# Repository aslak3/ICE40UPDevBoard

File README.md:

# ICE40UPDevBoard: an iCE40UP5K development board

## Features

The specification for this development board is as follows:

* [iCE40UP5K](https://www.latticesemi.com/view_document?document_id=51968) in QFN
* [N25Q032A](https://docs.rs-online.com/0866/0900766b80f7f8ab.pdf) 32 Mbit SPI flash
* DB15 VGA port:
  * [ADV7123](https://www.analog.com/media/en/technical-documentation/data-sheets/ADV7123-EP.pdf) RGB DAC
* PS/2 port with two channels for a mouse and keyboard
* I2C:
  * [DS3231M](https://www.analog.com/media/en/technical-documentation/data-sheets/ds3231m.pdf) RTC
  * [AT24C64](https://ww1.microchip.com/downloads/en/devicedoc/doc0336.pdf) EEPROM
  * Header for I2C connections
* 3 LEDs and a button
* User header with 6 available FPGA pins
* Powered by a 5V switching regulator (eg a 5V [PM05S050A](https://filecenter.deltaww.com/products/download/01/0102/datasheet/DS_PM05S.pdf)) and a barrel jack

A [schematic](ICE40UPDevBoard.pdf) is included here, along with the
[KiCAD](https://www.kicad.org) data files, whcih are in  KiCAD 6 format.

## PCB design

The PCB is a 4 layer board.  My boards were manufactured by
[JLCPCB](https://www.jlcpcb.com).

## Using

The jumper mechanism to route the SPI signals which carry the configuration
data from the programmer was borrowed directly from the [Lattice’s iCE40
UltraPlus Breakout
Board](https://www.latticesemi.com/view_document?document_id=51987).

Any iCE40 compatible programmer should be useable.  I built my own, out of a
Pi Pico, which is documented in [another repo](https://github.com/aslak3/spi-flasher).
The programmer has been used to program both the attached flash and the FPGA directly.

## Possible gotchas

The design of this board is a very slightly tweaked version of the build I
have on my bench.  I have tweaked the LED and button connection after
finding out that the three LED pins on the iCE40UP cannot source current for
an LED and must sink it instead.

The following features have not been tested yet:

* I2C bus and peripheral ICs
* PS/2 port

## Blog

The best place to learn about this board is undoubtably [my
blog](https://www.aslak.net/), including this post:

* [Design and build of a Lattice iCE40UP development board](https://www.aslak.net/index.php/2024/01/31/design-and-build-of-a-lattice-ice40up-development-board/)

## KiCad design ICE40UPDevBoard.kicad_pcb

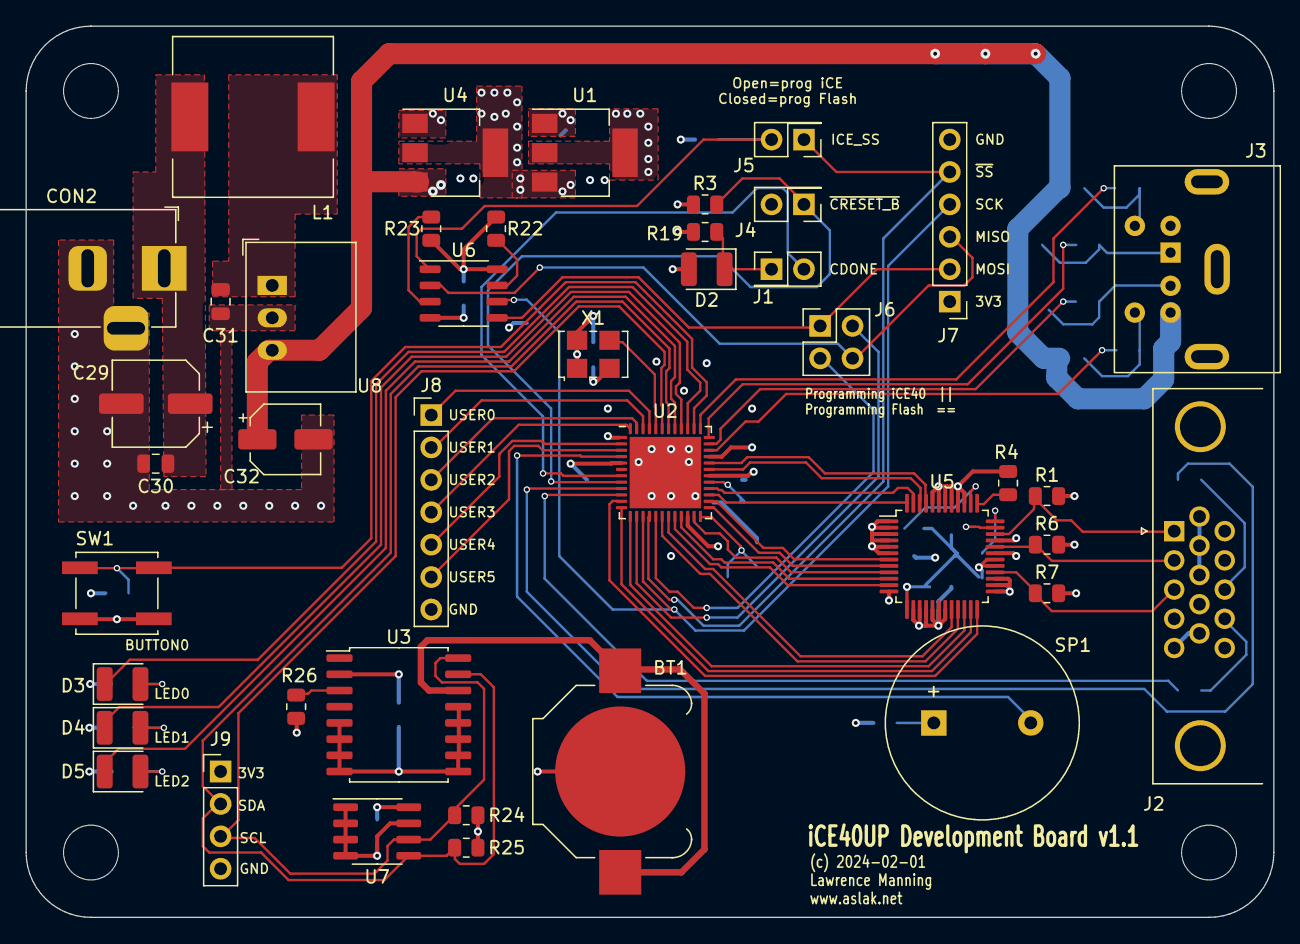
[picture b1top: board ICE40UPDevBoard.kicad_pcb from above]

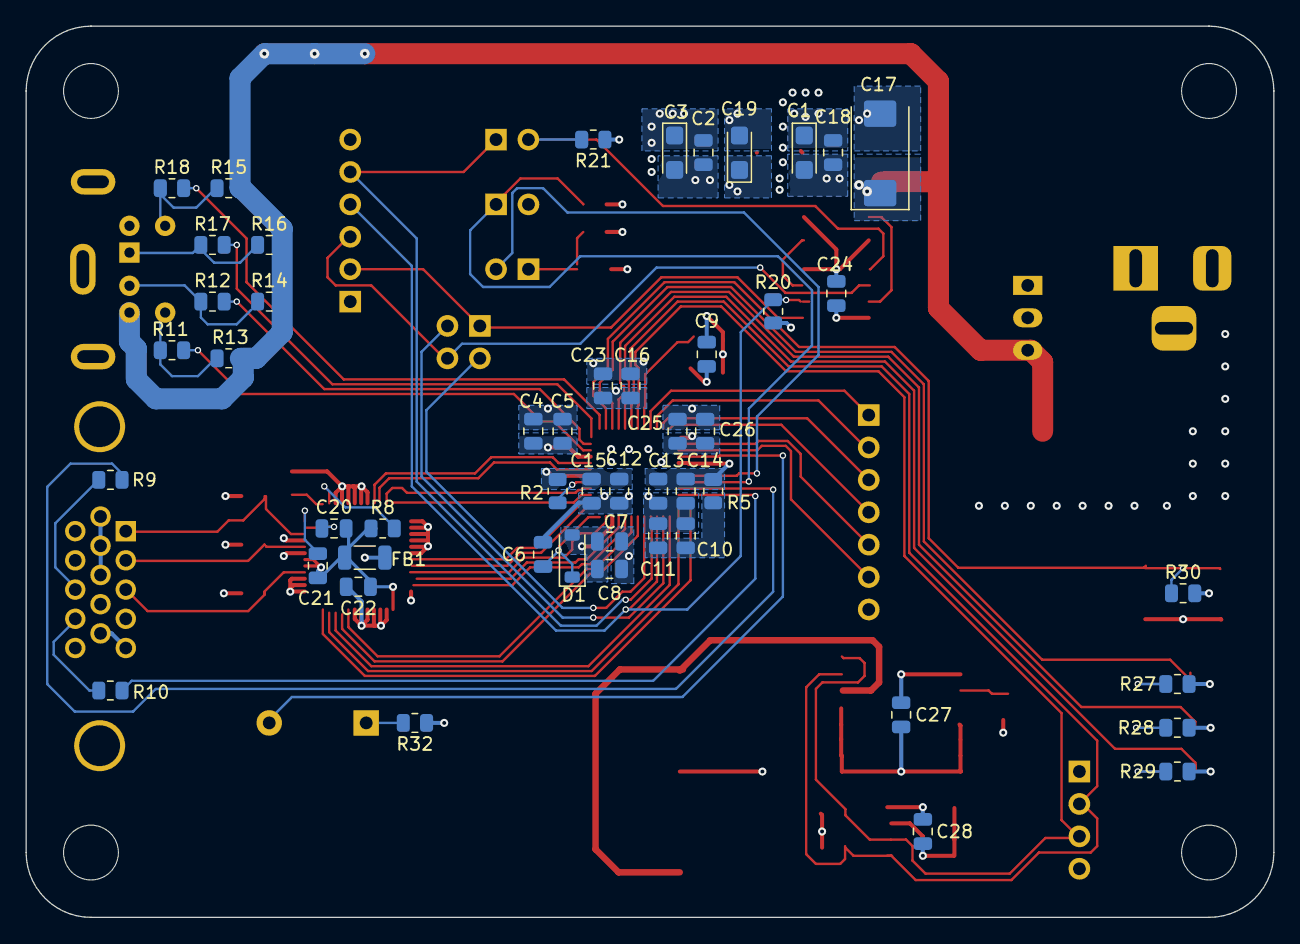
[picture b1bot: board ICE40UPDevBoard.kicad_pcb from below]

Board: 4 copper layers, 97.8 x 69.8 mm, 96 parts (50 on the bottom side), 75 nets.

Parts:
BT1: Battery_Cell; BatteryHolder_Keystone_3000_1x12mm
C1, C3, C19: 10u; CP_EIA-3216-10_Kemet-I
C2, C4, C6, C7, C9, C12, C13, C18, C20, C21, C22, C24, C25, C27, C28: 0.1u; C_0805_2012Metric
C5, C8, C14, C15, C26: 10n; C_0805_2012Metric
C10, C16, C30: 10u; C_0805_2012Metric
C11, C23: 100n; C_0805_2012Metric
C17: 47u; CP_EIA-7343-15_Kemet-W
C29: 470u; CP_Elec_6.3x7.7
C31: 4.7u; C_0805_2012Metric
C32: 10u; CP_Elec_5x5.7
CON2: POWERLJACK; BarrelJack_Horizontal
D1: MBR130; D_SOD-123
D2, D3, D4, D5: CDONE_LED; LED_1210_3225Metric
FB1: Bead; L_1206_3216Metric
H1, H2, H3, H4: HOLE; MountingHole_4.3mm_M4
J1, J4, J5: Conn_02x01; PinHeader_2x01_P2.54mm_Vertical
J2: DB15HD_FEMALE_SVGA; DSUB-15-HD_Female_Horizontal_P2.29x1.98mm_EdgePinOffset3.03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
J3: Mini-DIN-6; Connector_Mini-DIN_Female_6Pin_2rows
J6: Conn_02x02_Odd_Even; PinHeader_2x02_P2.54mm_Vertical
J7: Conn_01x06; PinHeader_1x06_P2.54mm_Vertical
J8: Conn_01x07; PinHeader_1x07_P2.54mm_Vertical
J9: Conn_01x04; PinHeader_1x04_P2.54mm_Vertical
L1: 10u; L_12x12mm_H4.5mm
R1, R6, R7: 75; R_0805_2012Metric
R2, R5: 100; R_0805_2012Metric
R3, R20, R21, R22, R23: 10K; R_0805_2012Metric
R4: 530; R_0805_2012Metric
R8, R13, R14, R15, R16, R24, R25, R26, R30: 4.7K; R_0805_2012Metric
R9, R10: 47; R_0805_2012Metric
R11, R12, R17, R18: 120; R_0805_2012Metric
R19, R27, R28, R29, R32: 1K; R_0805_2012Metric
SP1: BUZZER; Buzzer_15x7.5RM7.6
SW1: RESETBUTTON; SW_Push_1P1T_NO_CK_KSC6xxJ
U1: AZ1117-1.2; SOT-223-3_TabPin2
U2: ICE40UP5K-SG48ITR; QFN-48-1EP_7x7mm_P0.5mm_EP5.6x5.6mm
U3: DS3231M; SOIC-16W_7.5x10.3mm_P1.27mm
U4: AZ1117-3.3; SOT-223-3_TabPin2
U5: ADV7123KSTZ140; LQFP-48_7x7mm_P0.5mm
U6: N25Q032A13ESC40F; SOP-8_3.9x4.9mm_P1.27mm
U7: AT24CS64-SSHM; SOIC-8_3.9x4.9mm_P1.27mm
U8: R-78B5.0-2.0; Converter_DCDC_RECOM_R-78E-0.5_THT
X1: MPUOSC; Oscillator_SMD_SeikoEpson_SG8002LB-4Pin_5.0x3.2mm

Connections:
+1V2: C2.1, C3.1, C12.1, C13.1, C14.1, C15.1, C16.1, C23.1, R2.1, R5.1, U1.2 (VO), U2.5 (VCC), U2.30 (VCC)
+3.3VDAC: C20.2, C21.2, C22.1, FB1.1, R8.1, U5.13 (VAA), U5.29 (VAA), U5.30 (VAA)
+3V3: C1.1, C4.1, C5.1, C7.1, C8.1, C9.1, C18.1, C19.1, C24.1, C25.1, C26.1, C27.1, C28.1, D1.2 (A), D2.2 (A), FB1.2, J7.1, J9.1, R3.1, R20.1, R21.1, R22.1, R23.1, R24.1, R25.1, R26.1, R27.2, R28.2, R29.2, R30.2, U1.3 (VI), U2.1 (VCCIO_2), U2.22 (SPI_VCCIO1), U2.33 (VCCIO_0), U3.2 (VCC), U4.2 (VO), U6.8 (VCC), U7.8 (VCC), X1.1 (OE), X1.4 (Vcc)
+5V: C17.1, C32.1, J3.4, R13.2, R14.2, R15.2, R16.2, U4.3 (VI), U8.3 (+Vout)
/CDONE: J1.2, U2.7 (CDONE)
/FLASH_MISO: J6.4, J7.3, U6.2 (DO(IO1))
/FLASH_MOSI: J6.1, J7.2, U6.5 (DI(IO0))
/ICE_MISO: J6.2, U2.14 (IOB_32a_SPI_SO)
/ICE_MOSI: J6.3, U2.17 (IOB_33b_SPI_SI)
/ICE_SCK: J7.4, R20.2, U2.15 (IOB_34a_SPI_SCK), U6.6 (CLK)
/ICE_SS: J5.1, J7.5, U2.16 (IOB_35b_SPI_SS)
/Other/VBAT: BT1.1 (+), U3.14 (VBAT)
/VCCEXT: C29.1, C30.1, CON2.1, L1.1
/VCCEXTI: C31.1, L1.2, U8.1 (+Vin)
/VCCPLL: C10.1, C11.1, R5.2
/VPP_2V5: C6.1, D1.1 (K), U2.24 (VPP_2V5)
/~CRESET_B: J4.1, R3.2, U2.8 (~CRESET)
BLUE: J2.3, R7.1, U5.28 (IOB)
BLUE0: U2.19 (IOB_29b), U5.20 (B6)
BLUE1: U2.18 (IOB_31b), U5.21 (B7)
BLUE2: U2.13 (IOB_24a), U5.22 (B8)
BLUE3: U2.12 (IOB_22a), U5.23 (B9)
BUTTON0: R30.1, SW1.1, U2.38 (IOT_50b)
BUZZER: SP1.2, U2.4 (IOB_8a)
DACCLK: U2.11 (IOB_20a), U5.24 (CLOCK)
GLOBAL_CLK: U2.44 (IOB_3b_G6), X1.3 (OUT)
GND: BT1.2 (-), C1.2, C2.2, C3.2, C4.2, C5.2, C6.2, C7.2, C8.2, C9.2, C10.2, C11.2, C12.2, C13.2, C14.2, C15.2, C16.2, C17.2, C18.2, C19.2, C22.2, C23.2, C24.2, C25.2, C26.2, C27.2, C28.2, C29.2, C30.2, C31.2, C32.2, CON2.2, CON2.3, J2.0, J2.5, J2.6, J2.7, J2.8, J2.10, J3.3, J4.2, J7.6, J8.7, J9.4, R1.2, R4.2, R6.2, R7.2, R19.2, R32.1, SW1.2, U1.1 (GND), U2.49 (GND), U3.5 (GND), U3.6 (GND), U3.7 (GND), U3.8 (GND), U3.9 (GND), U3.10 (GND), U3.11 (GND), U3.12 (GND), U3.13 (GND), U4.1 (GND), U5.1 (G0), U5.2 (G1), U5.3 (G2), U5.4 (G3), U5.5 (G4), U5.6 (G5), U5.12 (~SYNC), U5.14 (B0), U5.15 (B1), U5.16 (B2), U5.17 (B3), U5.18 (B4), U5.19 (B5), U5.25 (GND), U5.26 (GND), U5.27 (~IOB), U5.31 (~IOG), U5.33 (~IOR), U5.39 (R0), U5.40 (R1), U5.41 (R2), U5.42 (R3), U5.43 (R4), U5.44 (R5), U6.4 (GND), U7.1 (A0), U7.2 (A1), U7.3 (A2), U7.4 (GND), U7.7 (WP), U8.2 (GND), X1.2 (GND)
GREEN: J2.2, R6.1, U5.32 (IOG)
GREEN0: U2.26 (IOT_39a), U5.7 (G6)
GREEN1: U2.25 (IOT_36b), U5.8 (G7)
GREEN2: U2.23 (IOT_37a), U5.9 (G8)
GREEN3: U2.21 (IOB_23b), U5.10 (G9)
HSYNC: R9.1, U2.9 (IOB_16a)
I2C_SCL: J9.3, R24.2, U2.43 (IOT_49a), U3.16 (SCL), U7.6 (SCL)
I2C_SDA: J9.2, R25.2, U2.42 (IOT_51a), U3.15 (SDA), U7.5 (SDA)
LED0: D3.1 (K), U2.39 (RGB0)
LED1: D4.1 (K), U2.40 (RGB1)
LED2: D5.1 (K), U2.41 (RGB2)
unnamed: D2.1 (K), J1.1, R19.1
unnamed: D3.2 (A), R27.1
unnamed: D4.2 (A), R28.1
unnamed: D5.2 (A), R29.1
unnamed: J2.13, R9.2
unnamed: J2.14, R10.2
unnamed: J3.1, R16.1, R17.1
unnamed: J3.2, R12.2, R14.1
unnamed: J3.5, R15.1, R18.1
unnamed: J3.6, R11.2, R13.1
unnamed: J5.2, R21.2, U6.1 (~CS)
unnamed: R32.2, SP1.1
unnamed: R2.2, U2.29 (VCCPLL)
unnamed: C20.1, U5.35 (COMP)
unnamed: R4.1, U5.37 (RSET)
unnamed: C21.1, U5.36 (VREF)
unnamed: R8.2, U5.38 (~PSAVE)
unnamed: R23.2, U6.3 (IO2)
unnamed: R22.2, U6.7 (IO3)
PS2ACLK: R18.2, U2.37 (IOT_45a_G1)
PS2ADATA: R17.2, U2.36 (IOT_48b)
PS2BCLK: R11.1, U2.34 (IOT_44b)
PS2BDATA: R12.1, U2.35 (IOT_46b_G0)
RED: J2.1, R1.1, U5.34 (IOR)
RED0: U2.32 (IOT_43a), U5.45 (R6)
RED1: U2.31 (IOT_42b), U5.46 (R7)
RED2: U2.28 (IOT_41a), U5.47 (R8)
RED3: U2.27 (IOT_38b), U5.48 (R9)
RTCSQWAVE: R26.2, U3.3 (~INT/SQW)
USER0: J8.1, U2.45 (IOB_5b)
USER1: J8.2, U2.46 (IOB_0a)
USER2: J8.3, U2.47 (IOB_2a)
USER3: J8.4, U2.48 (IOB_4a)
USER4: J8.5, U2.2 (IOB_6a)
USER5: J8.6, U2.3 (IOB_9b)
VSYNC: R10.1, U2.10 (IOB_18a)
~VGABLANK: U2.20 (IOB_25b_G3), U5.11 (~BLANK)

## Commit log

2024-02-02 Update the gerbers
    Weren't completely up to date with the latest tweaks.

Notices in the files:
ICE40UPDevBoard.kicad_pcb:
(c) 2024-02-01
